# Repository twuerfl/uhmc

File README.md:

# UHMC – Underfloor Heating Manifold Controller

**UHMC** (Underfloor Heating Manifold Controller) is a modular, ESP32-based controller designed for precise regulation of underfloor heating circuits. It integrates advanced control features while remaining cost-efficient and flexible for home automation setups.

---

## Features

- **Microcontroller:** ESP32-WROOM-32E
- **Connectivity:**
  - Ethernet via LAN8720A **OR** WIFI
  - Optional USB via CP2102N (default not populated to reduce cost)
- **Heating Circuit Control:**
  - 12 heating circuits (loops) total
  - Circuits 11 and 12 share two outputs for double current capacity
- **Driver Hardware:**
  - 2 × TPL7407LAPW motor drivers
  - Each driven via a SN74HC595PWR shift register
- **I²C Expansion:**
  - TCA9548AMRGER I²C multiplexer
  - Supports 8 separate I²C inputs
- **Firmware:** ESPHome

---

## Hardware Overview

| Component | Purpose |
|-----------|---------|
| ESP32-WROOM-32E | Main controller |
| LAN8720A | Ethernet interface |
| CP2102N | Optional USB for programming/debugging |
| TPL7407LAPW | 7-channel motor drivers for valve actuation |
| SN74HC595PWR | Shift registers to extend GPIOs for TPL7407LAPW |
| TCA9548AMRGER | I²C multiplexer for up to 8 I²C inputs |

---

## System Architecture
ESP32

->  SN74HC595  ->   TPL7407LAPW  ->  Heating Circuits 1-12

->  TCA9548AM  ->   I²C Sensors

->  LAN8720A   ->   Ethernet

->  CP2102N    ->   Optional USB

- Heating circuits 11 and 12 are paralleled for higher current capacity.
- ESPHome handles PID control, sensor input, and automation integration.

---

## Features in ESPHome

- Supports up to 12 heating circuits with PWM control
- I²C sensor integration via TCA9548 multiplexer
- Optional integration with Home Assistant
- Ethernet connectivity for remote monitoring and updates
- Modular configuration allowing flexible re-assignment of heating circuits

---

## License

CC BY-NC-SA 4.0
https://creativecommons.org/licenses/by-nc-sa/4.0/

---

## Notes

- USB interface is optional to save cost; populated only if needed.
- Firmware is configured via ESPHome YAML files for easy customization.

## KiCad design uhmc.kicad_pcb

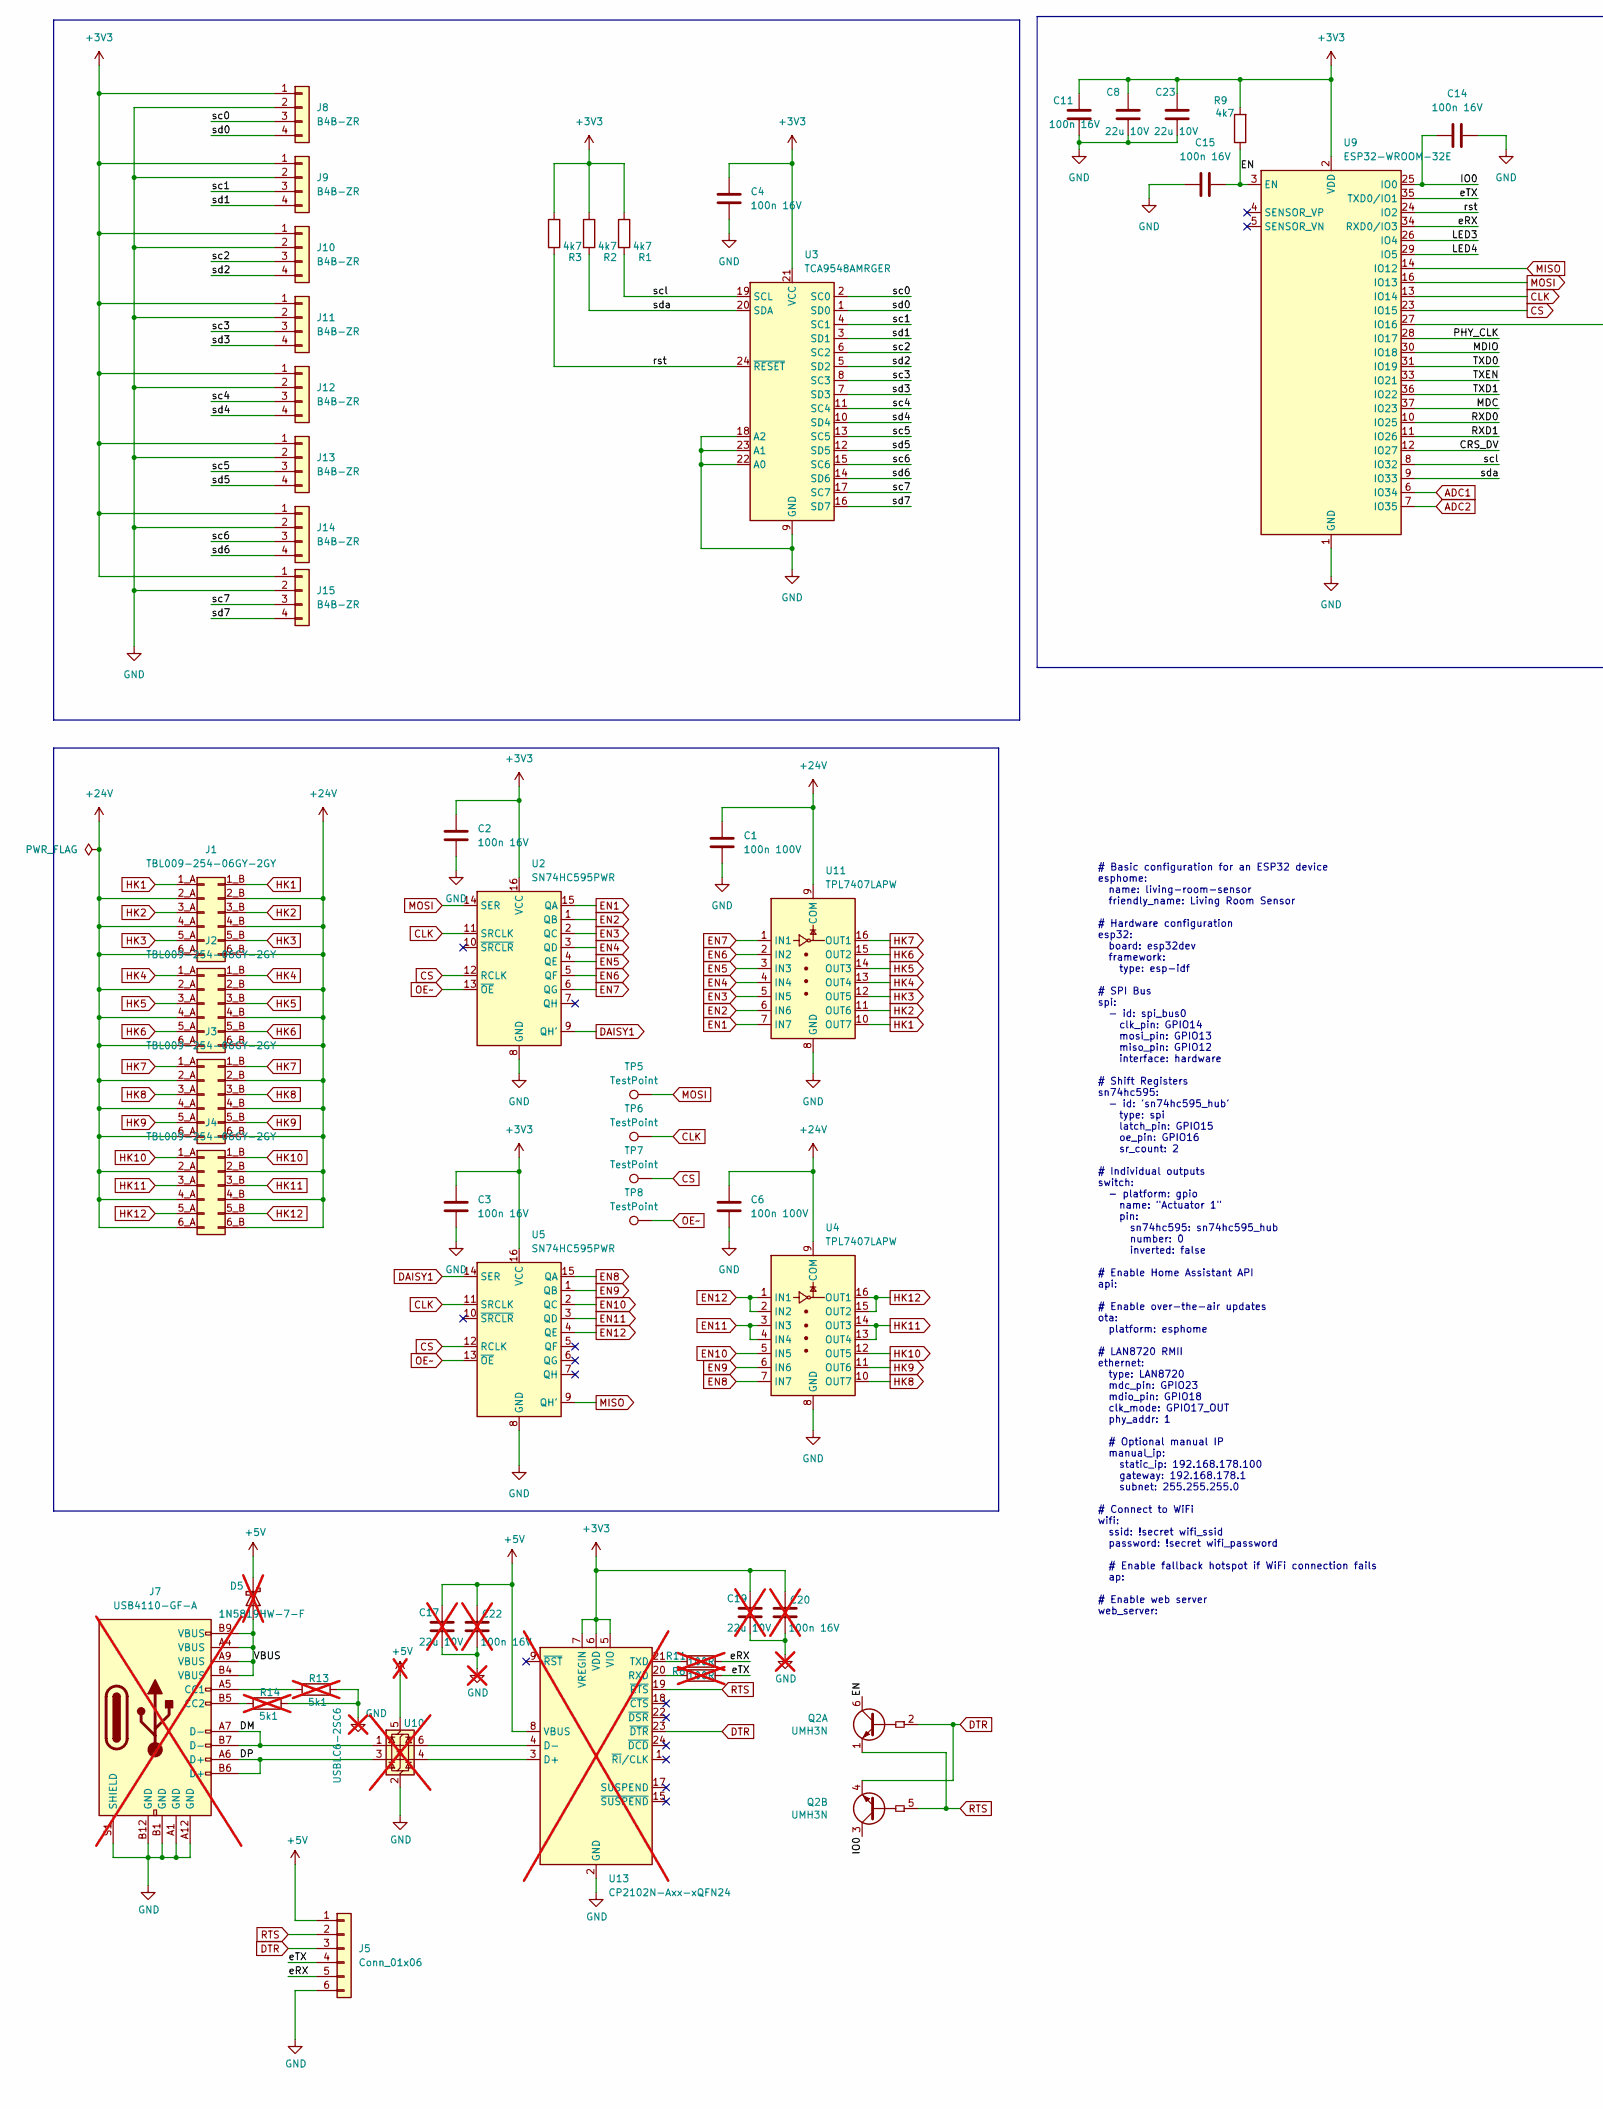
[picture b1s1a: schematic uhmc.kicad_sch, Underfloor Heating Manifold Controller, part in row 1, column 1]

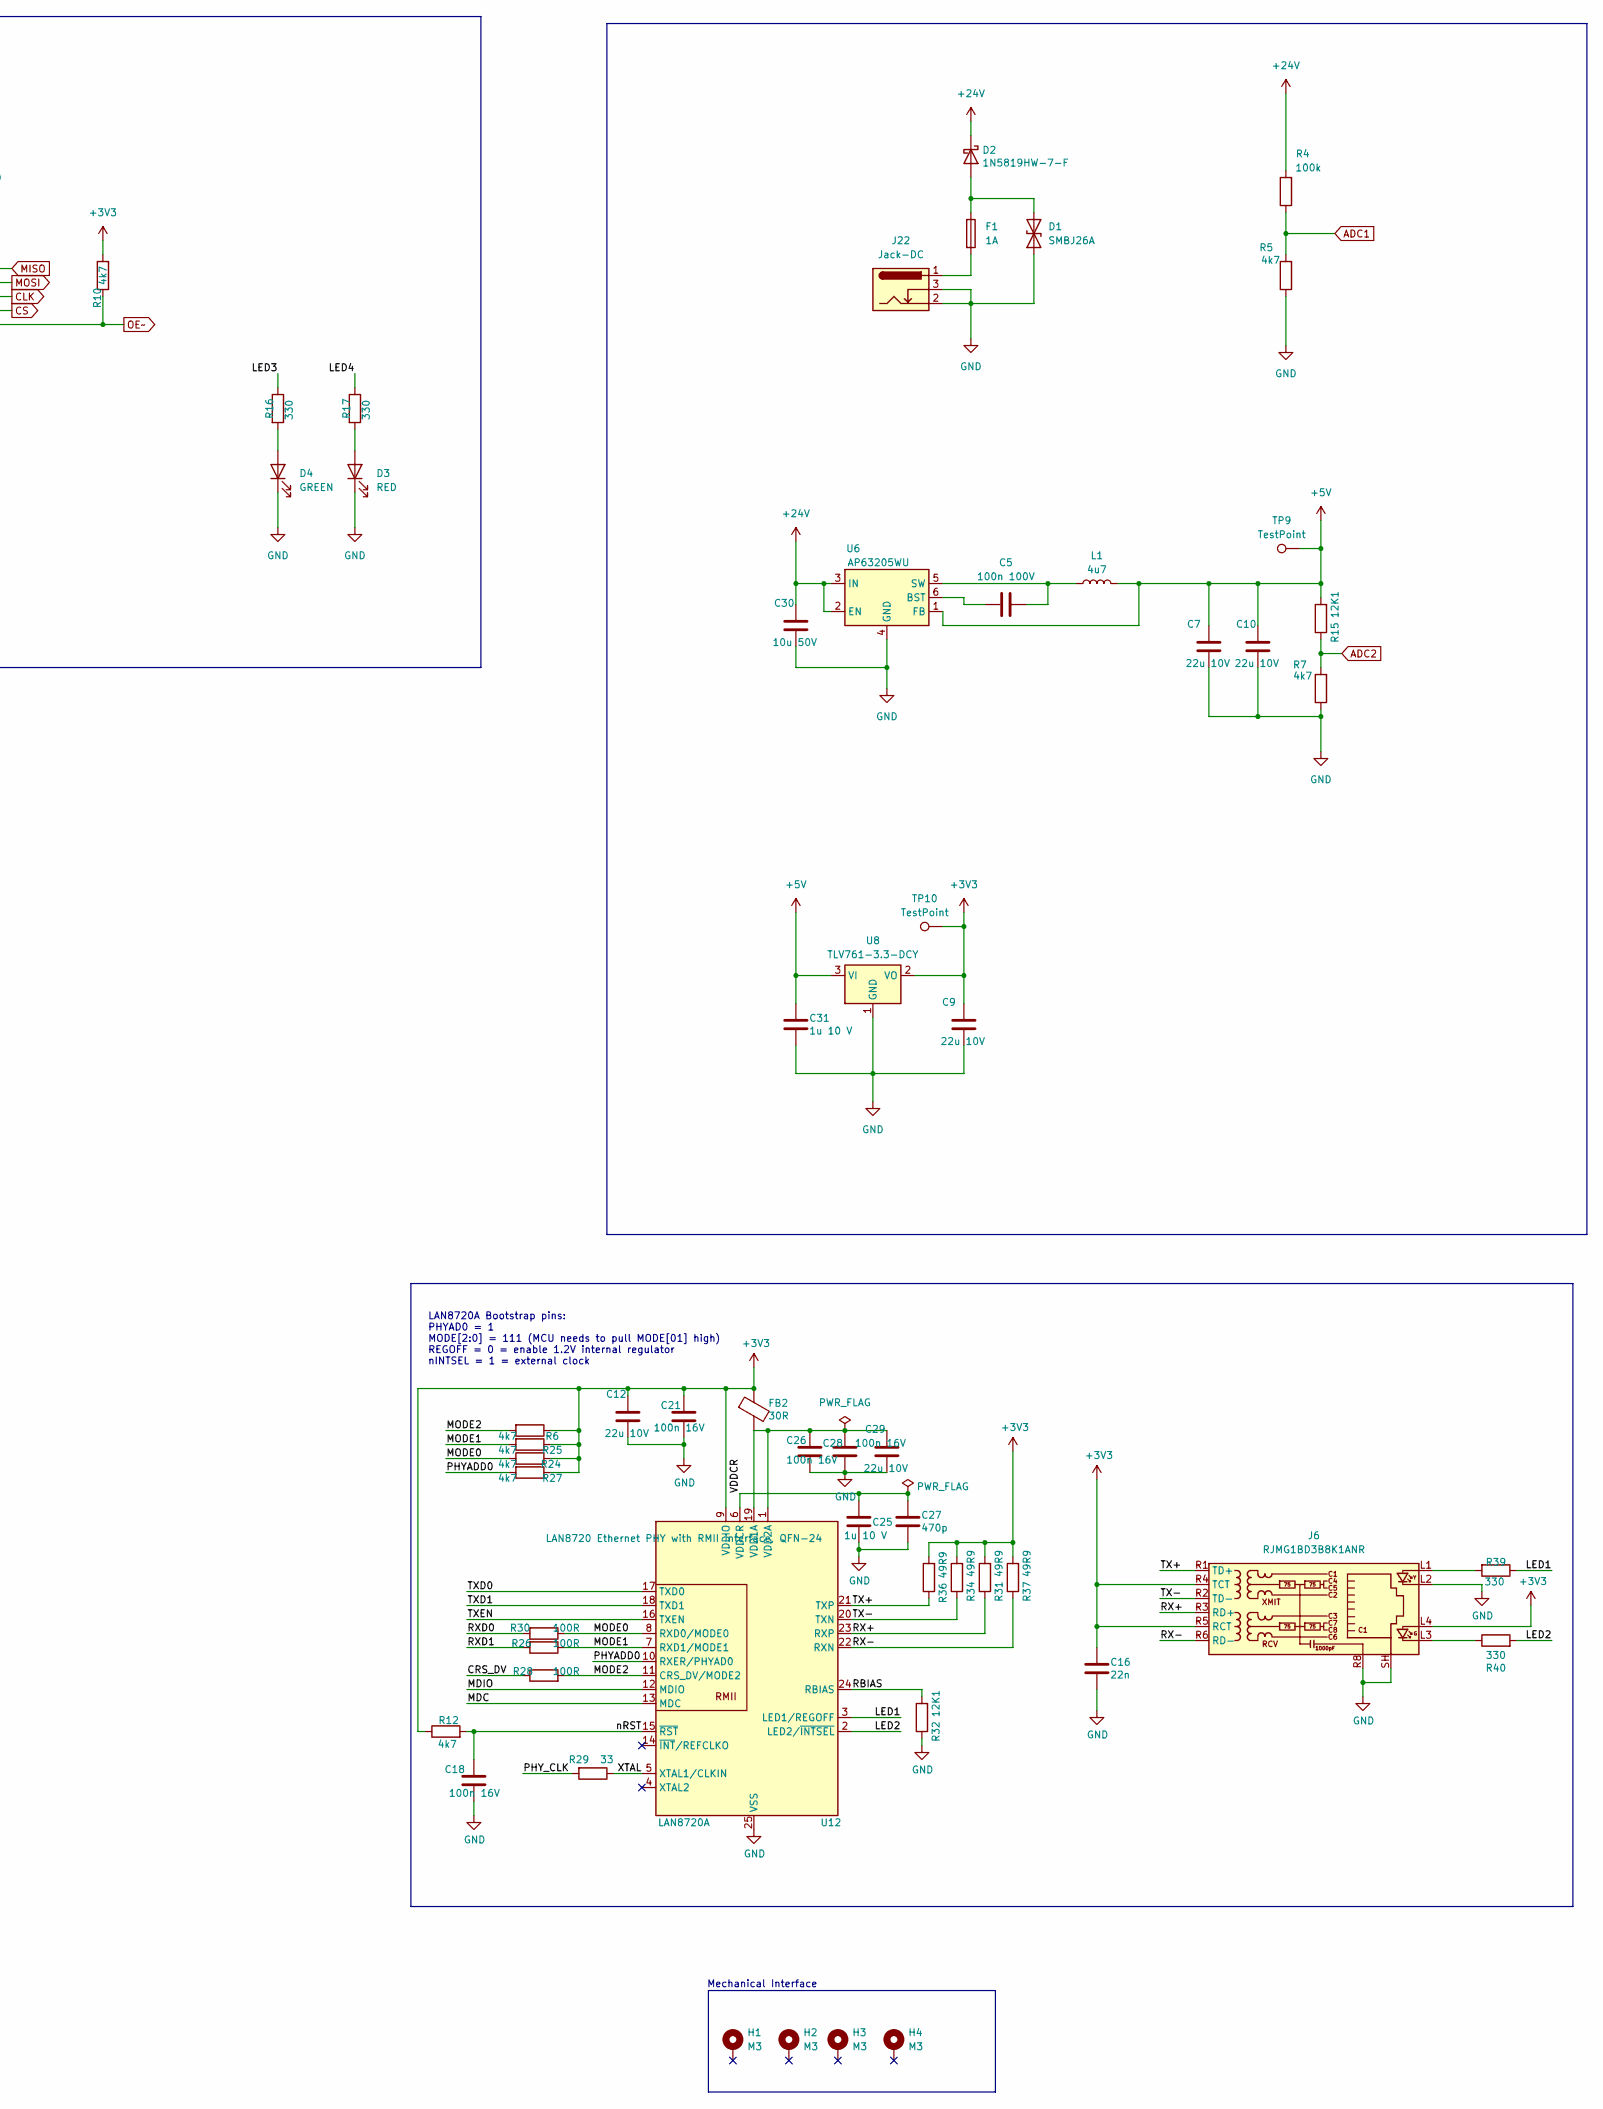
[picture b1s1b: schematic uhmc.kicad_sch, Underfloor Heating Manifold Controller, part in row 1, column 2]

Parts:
C1, C5, C6: 100n 100V; C_0603_1608Metric; MPN CL10B104KC8NNNC
C2, C3, C4, C11, C14, C15, C18, C21, C26, C28: 100n 16V; C_0603_1608Metric; MPN CL10B104KO8NFNC
C7, C8, C9, C10, C12, C23, C29: 22u 10V; C_0603_1608Metric; MPN GRM188R61A226ME15D
C16: 22n; C_0603_1608Metric; MPN CL10B223KB8NNNC
C17, C19: 22u 10V; C_0603_1608Metric; MPN GRM188R61A226ME15D; not fitted
C20, C22: 100n 16V; C_0603_1608Metric; MPN CL10B104KO8NFNC; not fitted
C25, C31: 1u 10 V; C_0603_1608Metric; MPN C0603C105K8RACTU
C27: 470p; C_0603_1608Metric; MPN CL10B102KB8NNNC
C30: 10u 50V; C_1206_3216Metric; MPN CL31A106KBHNNNE
D1: SMBJ26A; D_SMB; MPN SMBJ26A-13-F
D2: 1N5819HW-7-F; D_SOD-123; MPN 1N5819HW-7-F
D3: RED; LED_0603_1608Metric; MPN LTST-C193KRKT-5A
D4: GREEN; LED_0603_1608Metric; MPN LTST-C193KGKT-5A
D5: 1N5819HW-7-F; D_SOD-123; MPN 1N5819HW-7-F; not fitted
F1: 1A; Fuseholder_Clip-5x20mm_Bel_FC-203-22_Lateral_P17.80x5.00mm_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; MPN FC-203
FB2: 30R; L_0603_1608Metric; MPN WLBD1608HCU601TH
H1, H2, H3, H4: M3; MountingHole_3.2mm_M3_ISO7380_Pad
J1, J2, J3, J4: TBL009-254-06GY-2GY; CUI_TBL009-254-06BE-2BE; MPN TBL009-254-06GY-2GY
J5: Conn_01x06; PinHeader_1x06_P1.27mm_Vertical; MPN M50-3530642
J6: RJMG1BD3B8K1ANR; RJ45_Amphenol_RJMG1BD3B8K1ANR; MPN RJMG1BD3B8K1ANR
J7: USB4110-GF-A; USB_C_Receptacle_GCT_USB4110; MPN USB4110-GF-A; not fitted
J8, J9, J10, J11, J12, J13, J14, J15: B4B-ZR; JST_ZH_B4B-ZR_1x04_P1.50mm_Vertical; MPN B4B-ZR
J22: Jack-DC; Tensility 54-00164_SMT_Horizontal; MPN 54-00164
L1: 4u7; L_Bourns-SRN4018; MPN SRN4018-4R7M
Q2: UMH3N; SOT-363_SC-70-6; MPN UMH3NFHATN
R1, R2, R3, R5, R6, R7, R9, R10, R12, R24, R25, R27: 4k7; R_0603_1608Metric; MPN RC0603FR-074K7L
R4: 100k; R_0603_1608Metric; MPN RC0603FR-07100KL
R8, R11: 100R; R_0603_1608Metric; MPN RC0603FR-07100RP; not fitted
R13, R14: 5k1; R_0603_1608Metric; MPN RC0603FR-075K1L; not fitted
R15, R32: 12K1; R_0603_1608Metric; MPN RC0603FR-0712K1L
R16, R17, R39, R40: 330; R_0603_1608Metric; MPN RC0603FR-07330RL
R26, R28, R30: 100R; R_0603_1608Metric; MPN RC0603FR-07100RP
R29: 33; R_0603_1608Metric; MPN RC0603FR-0733RL
R31, R34, R36, R37: 49R9; R_0603_1608Metric; MPN RC0603FR-0749R9L
TP5, TP6, TP7, TP8, TP9, TP10: TestPoint; TestPoint_Pad_D1.0mm
U2, U5: SN74HC595PWR; TSSOP-16_4.4x5mm_P0.65mm; MPN SN74HC595PWR
U3: TCA9548AMRGER; Texas_RGE0024C_VQFN-24-1EP_4x4mm_P0.5mm_EP2.1x2.1mm; MPN TCA9548AMRGER
U4, U11: TPL7407LAPW; TSSOP-16_4.4x5mm_P0.65mm; MPN TPL7407LAPW
U6: AP63205WU; TSOT-23-6; MPN AP63205WU
U8: TLV761-3.3-DCY; SOT-223-3_TabPin2; MPN TLV76133DCYR
U9: ESP32-WROOM-32E; MPN ESP32-WROOM-32E-N8
U10: USBLC6-2SC6; SOT-23-6; MPN USBLC6-2SC6; not fitted
U12: LAN8720A; VQFN-24-1EP_4x4mm_P0.5mm_EP2.5x2.5mm; MPN LAN8720A-CP
U13: CP2102N-Axx-xQFN24; QFN-24-1EP_4x4mm_P0.5mm_EP2.6x2.6mm; MPN CP2102C-A01-GQFN24; not fitted

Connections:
+3V3: C2.2, C3.2, C4.2, C8.1, C9.1, C11.2, C12.1, C16.1, C19.1, C20.1, C21.1, C23.1, FB2.1, J6.L4, J6.R4 (TCT), J6.R5 (RCT), J8.1, J9.1, J10.1, J11.1, J12.1, J13.1, J14.1, J15.1, R1.1, R2.1, R3.1, R6.1, R9.2, R10.2, R12.1, R24.2, R25.1, R27.1, R31.2, R34.2, R36.2, R37.2, TP10.1, U2.16 (VCC), U3.21 (VCC), U5.16 (VCC), U8.2 (VO), U9.2 (VDD), U12.9 (VDDIO), U13.5 (VIO), U13.6 (VDD), U13.7 (VREGIN)
+5V: C7.1, C10.1, C17.1, C22.1, C31.1, D5.1 (K), J5.1, L1.2, R15.2, TP9.1, U6.1 (FB), U8.3 (VI), U10.5 (VBUS), U13.8 (VBUS)
+24V: C1.1, C6.1, C30.1, D2.1 (K), J1.2_A (Pin_2a), J1.2_B (Pin_2b), J1.4_A (Pin_4a), J1.4_B (Pin_4b), J1.6_A (Pin_6a), J1.6_B (Pin_6b), J2.2_A (Pin_2a), J2.2_B (Pin_2b), J2.4_A (Pin_4a), J2.4_B (Pin_4b), J2.6_A (Pin_6a), J2.6_B (Pin_6b), J3.2_A (Pin_2a), J3.2_B (Pin_2b), J3.4_A (Pin_4a), J3.4_B (Pin_4b), J3.6_A (Pin_6a), J3.6_B (Pin_6b), J4.2_A (Pin_2a), J4.2_B (Pin_2b), J4.4_A (Pin_4a), J4.4_B (Pin_4b), J4.6_A (Pin_6a), J4.6_B (Pin_6b), R4.2, U4.9 (COM), U6.2 (EN), U6.3 (IN), U11.9 (COM)
/CRS_DV: R28.1, U9.12 (IO27)
/DM: J7.A7 (D-), J7.B7 (D-), U10.1 (I/O1)
/DP: J7.A6 (D+), J7.B6 (D+), U10.3 (I/O2)
/EN: C15.1, Q2.6 (C1), R9.1, U9.3 (EN)
/IO0: C14.2, Q2.3 (C2), U9.25 (IO0)
/LED1: R39.1, U12.3 (LED1/REGOFF)
/LED2: R40.2, U12.2 (LED2/~INTSEL)
/LED3: R16.1, U9.26 (IO4)
/LED4: R17.1, U9.29 (IO5)
/MDC: U9.37 (IO23), U12.13 (MDC)
/MDIO: U9.30 (IO18), U12.12 (MDIO)
/MODE0: R24.1, R30.1, U12.8 (RXD0/MODE0)
/MODE1: R25.2, R26.1, U12.7 (RXD1/MODE1)
/MODE2: R6.2, R28.2, U12.11 (CRS_DV/MODE2)
/PHYADD0: R27.2, U12.10 (RXER/PHYAD0)
/PHY_CLK: R29.2, U9.28 (IO17)
/RBIAS: R32.2, U12.24 (RBIAS)
/RX+: J6.R3 (RD+), R31.1, U12.23 (RXP)
/RX-: J6.R6 (RD-), R37.1, U12.22 (RXN)
/RXD0: R30.2, U9.10 (IO25)
/RXD1: R26.2, U9.11 (IO26)
/TX+: J6.R1 (TD+), R36.1, U12.21 (TXP)
/TX-: J6.R2 (TD-), R34.1, U12.20 (TXN)
/TXD0: U9.31 (IO19), U12.17 (TXD0)
/TXD1: U9.36 (IO22), U12.18 (TXD1)
/TXEN: U9.33 (IO21), U12.16 (TXEN)
/VBUS: D5.2 (A), J7.A4 (VBUS), J7.A9 (VBUS), J7.B4 (VBUS), J7.B9 (VBUS)
/VDDCR: C25.1, C27.1, U12.6 (VDDCR)
/XTAL: R29.1, U12.5 (XTAL1/CLKIN)
/eRX: J5.5, R11.1, U9.34 (RXD0/IO3)
/eTX: J5.4, R8.1, U9.35 (TXD0/IO1)
/nRST: C18.2, R12.2, U12.15 (~RST)
/rst: R3.2, U3.24 (~RESET), U9.24 (IO2)
/sc0: J8.3, U3.2 (SC0)
/sc1: J9.3, U3.4 (SC1)
/sc2: J10.3, U3.6 (SC2)
/sc3: J11.3, U3.8 (SC3)
/sc4: J12.3, U3.11 (SC4)
/sc5: J13.3, U3.13 (SC5)
/sc6: J14.3, U3.15 (SC6)
/sc7: J15.3, U3.17 (SC7)
/scl: R1.2, U3.19 (SCL), U9.8 (IO32)
/sd0: J8.4, U3.1 (SD0)
/sd1: J9.4, U3.3 (SD1)
/sd2: J10.4, U3.5 (SD2)
/sd3: J11.4, U3.7 (SD3)
/sd4: J12.4, U3.10 (SD4)
/sd5: J13.4, U3.12 (SD5)
/sd6: J14.4, U3.14 (SD6)
/sd7: J15.4, U3.16 (SD7)
/sda: R2.2, U3.20 (SDA), U9.9 (IO33)
ADC1: R4.1, R5.2, U9.6 (IO34)
ADC2: R7.2, R15.1, U9.7 (IO35)
CLK: TP6.1, U2.11 (SRCLK), U5.11 (SRCLK), U9.13 (IO14)
CS: TP7.1, U2.12 (RCLK), U5.12 (RCLK), U9.23 (IO15)
DAISY1: U2.9 (QH'), U5.14 (SER)
DTR: J5.3, Q2.2 (B1), Q2.4 (E2), U13.23 (~DTR)
EN1: U2.15 (QA), U11.7 (IN7)
EN2: U2.1 (QB), U11.6 (IN6)
EN3: U2.2 (QC), U11.5 (IN5)
EN4: U2.3 (QD), U11.4 (IN4)
EN5: U2.4 (QE), U11.3 (IN3)
EN6: U2.5 (QF), U11.2 (IN2)
EN7: U2.6 (QG), U11.1 (IN1)
EN8: U4.7 (IN7), U5.15 (QA)
EN9: U4.6 (IN6), U5.1 (QB)
EN10: U4.5 (IN5), U5.2 (QC)
EN11: U4.3 (IN3), U4.4 (IN4), U5.3 (QD)
EN12: U4.1 (IN1), U4.2 (IN2), U5.4 (QE)
GND: C1.2, C2.1, C3.1, C4.1, C6.2, C7.2, C8.2, C9.2, C10.2, C11.1, C12.2, C14.1, C15.2, C16.2, C17.2, C18.1, C19.2, C20.2, C21.2, C22.2, C23.2, C25.2, C26.1, C27.2, C28.1, C29.2, C30.2, C31.2, D1.1 (A1), D3.1 (K), D4.1 (K), J5.6, J6.L2, J6.R8, J6.SH, J7.A1 (GND), J7.A12 (GND), J7.B1 (GND), J7.B12 (GND), J7.S1 (SHIELD), J8.2, J9.2, J10.2, J11.2, J12.2, J13.2, J14.2, J15.2, J22.2, J22.3, R5.1, R7.1, R13.2, R14.2, R32.1, U2.8 (GND), U3.9 (GND), U3.18 (A2), U3.22 (A0), U3.23 (A1), U4.8 (GND), U5.8 (GND), U6.4 (GND), U8.1 (GND), U9.1 (GND), U9.15 (GND), U9.38 (GND), U9.39 (GND), U10.2 (GND), U11.8 (GND), U12.25 (VSS), U13.2 (GND), U13.25 (GND)
HK1: J1.1_A (Pin_1a), J1.1_B (Pin_1b), U11.10 (OUT7)
HK2: J1.3_A (Pin_3a), J1.3_B (Pin_3b), U11.11 (OUT6)
HK3: J1.5_A (Pin_5a), J1.5_B (Pin_5b), U11.12 (OUT5)
HK4: J2.1_A (Pin_1a), J2.1_B (Pin_1b), U11.13 (OUT4)
HK5: J2.3_A (Pin_3a), J2.3_B (Pin_3b), U11.14 (OUT3)
HK6: J2.5_A (Pin_5a), J2.5_B (Pin_5b), U11.15 (OUT2)
HK7: J3.1_A (Pin_1a), J3.1_B (Pin_1b), U11.16 (OUT1)
HK8: J3.3_A (Pin_3a), J3.3_B (Pin_3b), U4.10 (OUT7)
HK9: J3.5_A (Pin_5a), J3.5_B (Pin_5b), U4.11 (OUT6)
HK10: J4.1_A (Pin_1a), J4.1_B (Pin_1b), U4.12 (OUT5)
HK11: J4.3_A (Pin_3a), J4.3_B (Pin_3b), U4.13 (OUT4), U4.14 (OUT3)
HK12: J4.5_A (Pin_5a), J4.5_B (Pin_5b), U4.15 (OUT2), U4.16 (OUT1)
MISO: U5.9 (QH'), U9.14 (IO12)
MOSI: TP5.1, U2.14 (SER), U9.16 (IO13)
unnamed: D1.2 (A2), D2.2 (A), F1.1
unnamed: D3.2 (A), R17.2
unnamed: D4.2 (A), R16.2
unnamed: F1.2, J22.1
unnamed: J6.L1, R39.2
unnamed: J6.L3, R40.1
unnamed: J7.A5 (CC1), R13.1
unnamed: J7.B5 (CC2), R14.1
unnamed: C5.2, U6.6 (BST)
unnamed: C5.1, L1.1, U6.5 (SW)
unnamed: C26.2, C28.2, C29.1, FB2.2, U12.1 (VDD2A), U12.19 (VDD1A)
unnamed: U10.4 (I/O2), U13.3 (D+)
unnamed: U10.6 (I/O1), U13.4 (D-)
unnamed: R8.2, U13.20 (RXD)
unnamed: R11.2, U13.21 (TXD)
OE~: R10.1, TP8.1, U2.13 (~OE), U5.13 (~OE), U9.27 (IO16)
RTS: J5.2, Q2.1 (E1), Q2.5 (B2), U13.19 (~RTS)

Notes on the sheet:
# Basic configuration for an ESP32 device esphome: name: living-room-sensor friendly_name: Living Room Sensor # Hardware configuration esp32: board: esp32dev framework: type: esp-idf # SPI Bus spi: - id: spi_bus0 clk_pin: GPIO14 mosi_pin: GPIO13 miso_pin: GPIO12 interface: hardware # Shift Register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
LAN8720A Bootstrap pins: PHYAD0 = 1 MODE[2:0] = 111 (MCU needs to pull MODE[01] high) REGOFF = 0 = enable 1.2V internal regulator nINTSEL = 1 = external clock
Mechanical Interface

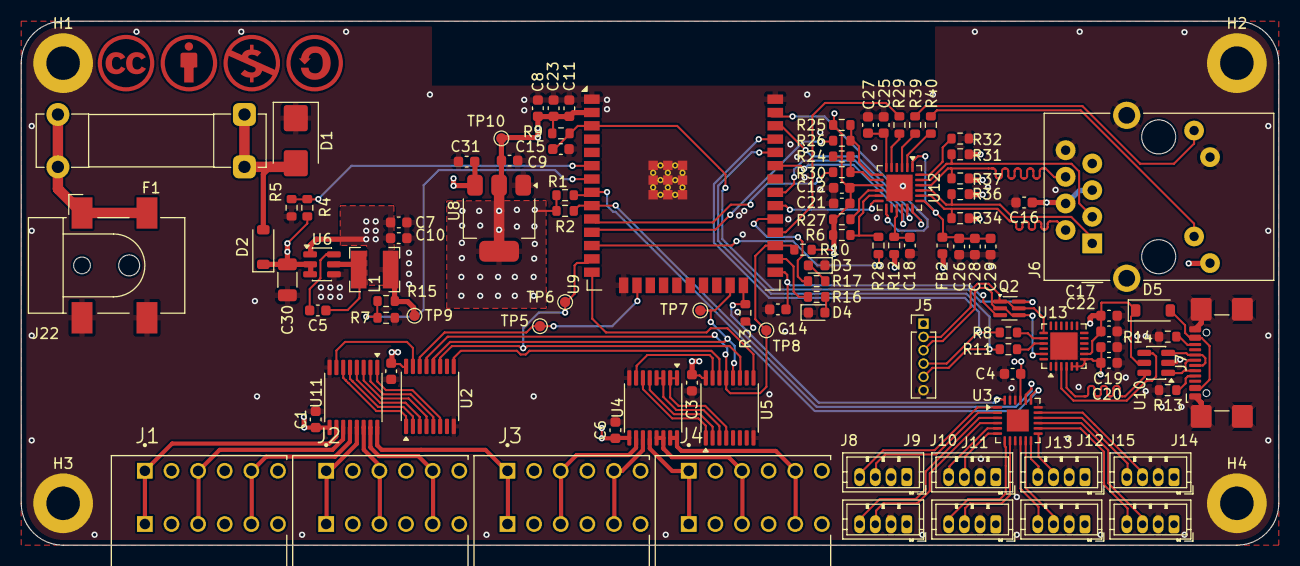
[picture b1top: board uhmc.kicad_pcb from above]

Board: 4 copper layers, 120.0 x 50.0 mm, 106 parts (0 on the bottom side), 104 nets.

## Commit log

2026-03-24 Create README.md for UHMC project
    Add initial README.md with project details and features.
2026-03-24 Improve formatting of system architecture in README
    Adjusted formatting for better readability in the system architecture section.
2026-03-24 Update system architecture formatting in README
    Reformatted system architecture section for clarity.
2026-03-24 Improve formatting of system architecture section
    Updated system architecture formatting for clarity.
2026-03-24 Format system architecture section in README
